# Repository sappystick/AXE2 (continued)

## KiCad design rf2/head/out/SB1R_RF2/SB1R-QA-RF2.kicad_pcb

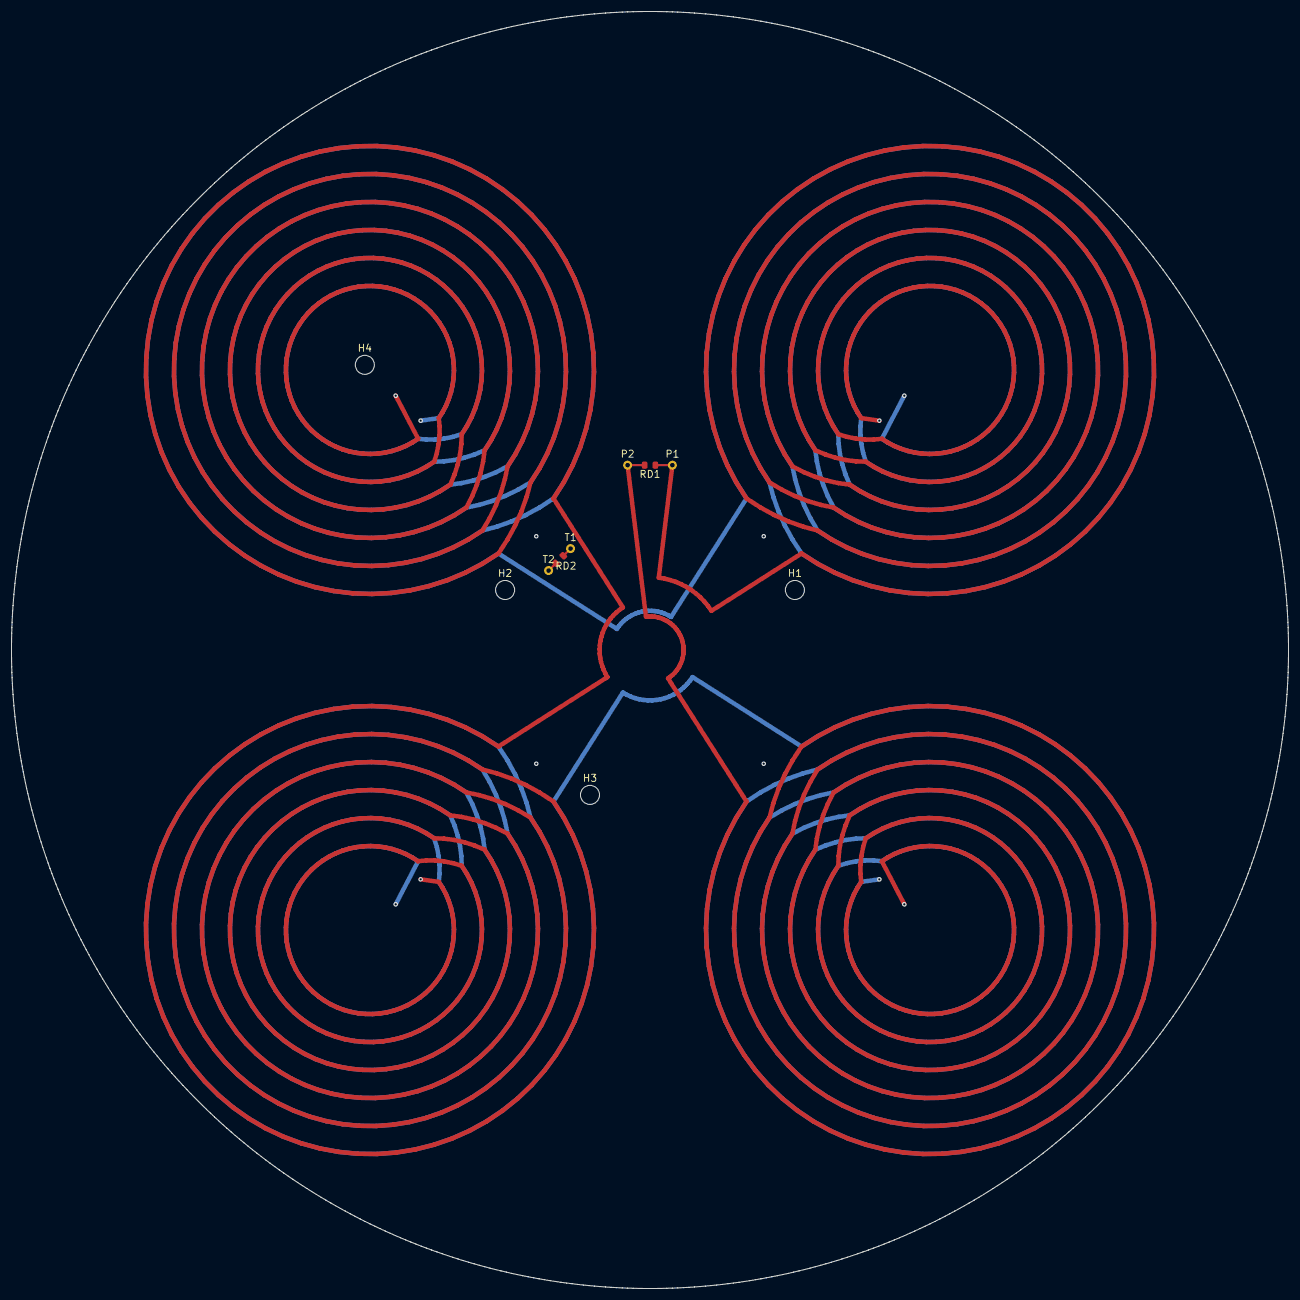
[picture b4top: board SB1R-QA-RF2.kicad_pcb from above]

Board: 4 copper layers, 228.0 x 228.0 mm, 10 parts (0 on the bottom side), 3 nets.

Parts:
H1, H2, H3, H4: MH_M3
P1, P2: LEAD_PAD
RD1, RD2: 680R 0.1% thin film 0805, non-magnetic terminatio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; R_0805_2012Metric
T1, T2: TRANSFER_PAD

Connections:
QA_COIL: P1.1, P2.1, RD1.1, RD1.2
QB_T1: RD2.1, T1.1
QB_T2: RD2.2, T2.1

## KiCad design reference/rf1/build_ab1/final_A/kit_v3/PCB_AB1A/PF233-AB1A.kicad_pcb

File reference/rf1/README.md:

# RF1: rigid-flex redesign, side experiment (started 2026-10-29)

**Status: MODELED side experiment, phase 1 done.** Not part of the sign-off, the pipeline, the regress suite or any release. The baseline design is read and never written: every input the study reads is recorded with its sha256 in `results/rf1_phase1.json` together with the baseline commit. Any generator that a later phase changes is first copied into `experiments/RF1_rigidflex/src/` and changed there.

**Fixed (owner, 2026-10-29):** receive coils SB1R-QA/QB, the HTA antenna, the six TX formers and their litz, every printed part. **Free:** how the electronics are split into boards and how they connect: flex, rigid-flex or the circular rigid boards.

## Concepts

| | A: catalog FFC (B12 decision) | B: soldered flex jumpers | C: head rigid-flex (RF1 main line) |
|---|---|---|---|
| What | separate rigid boards, 0.5 mm FFC + connectors at the duct edges | separate rigid boards, custom 2-layer flex strips soldered / hot-bar bonded to pads (no connector) | AB1A + AB1B + CB1D + LB1 one rigid-flex panel (6L rigid sections, 2L flex core), HTA a flex tail, SB1R leads a soldered flex jumper |
| Hand joints in the head (today 66) | 18 (LB1, HTA and SB1R wires stay; the link becomes 4 reflowed connectors) | 12 bonded ends | 5 |
| Boards testable alone | yes | yes | no (panel test + test pads) |
| Fab | standard | standard + simple flex | rigid-flex vendor, every change re-spins the panel |

## Phase 1 results (`rf1_study.py`, MODELED / mesh-checked)

| Question | Result |
|---|---|
| AB1 <-> CB1D link fit on the meshes (link_path_check, imported unchanged) | baseline IDC ribbon 6 / 16 FAIL; catalog FFC 0 / 14; rigid-flex hinge (0.2 mm, no connector) 0 / 14 |
| Headroom (rigid-flex hinge) | 10.4 mm under LB1 (ribbon -4.4, FFC 8.4), 7.2 mm under the septum (ribbon -2.6, FFC 5.2) |
| CB1D -> LB1 hinge, CB1D -> HTA tail | rise 10.6 / 15.9 mm, S-fold needs 8.0 mm at a 2.0 mm fold radius (10 x 0.2 mm): both fit; flex about 15 / 21 mm |
| Receive-coil lead pair, 60 mm | loop area 10.2 mm2 (AWG36 touching) to 60 mm2 (loose 1 mm) today, 3.0 mm2 fixed on a broadside flex pair; capacitance about 5 pF either way |
| Eddy rule 5 | the board graph is a tree (no closed loop around the axis); hatched planes in the hinges; FR4 / polyimide stiffeners only (the vendor also offers stainless and aluminium: excluded) |
| Vendor (Rigiflex pages, `ds/`) | D228 fits the 18 x 24 in panel; 0.10 / 0.10 mm trace / space covers our finest; 6L 1.6 mm rigid-flex with 1 oz is a listed build; polyimide er 4, DF 0.04, water absorption 2.9 % |

What this does **not** show yet: any change in leak, noise or detection. The loop-area ratio is geometry only; the pickup needs the TX field along the lead path (phase 2).

## Where the real improvement is

1. **Build quality and repeatability (large, near certain):** 66 -> 5 hand joints in the head; the receive-lead loop area becomes a fixed 3 mm2 instead of 10-60 mm2 that depends on dressing, so the air leak becomes a calibratable constant instead of a per-unit variable. This is the gain RF1 can deliver for sure.
2. **Receive chain clean-sheet (large, MODELED next):** the AB1 sections are laid out from scratch in RF1, so the known receive defects go in at the same time: VREF / VCM buffer stability (OPEN_ITEMS 30), OPA2211 input range (31), chip-orientation robustness (B11), header pad rings (33). These are performance items; the flex is what lets the layout start over without the header constraint.
3. **Digital noise next to the receive coils (medium, to be modeled):** the ADC SPI (SCLK >= 27.2 MHz) runs between hatched ground layers in the hinge instead of an open ribbon.
4. **Not changed by RF1:** TX (litz, 20 A, 460 V taps stay wire, rules 5 / 6), the shaft cords (a 356 mm telescoping stroke needs dynamic flex: not proposed), the neck and handle boards.

## Phases

1. **Done:** census, mesh fit, fold radii, lead loop area, loop check, vendor fit (`results/rf1_phase1.json`, `results/rf1_head_concept.png`).
2. Receive-lead pickup: copy `sbq_sim.py` into `src/`, add the flex-tail path and the TX field along it; leak and its spread (wire dress Monte Carlo vs fixed flex). Hinge crosstalk SCLK -> RX input.
3. Clean-sheet AB1 section: copy `afe_design.py` / `afe_layout.py` into `src/`, apply items 30 / 31 (isolation resistor or reference driver; VCM / amplifier choice) and the rotating decoupling group (B11); route with the repo router.
4. Rigid-flex board definition: one outline with rigid and flex regions, stackup drawing (6L rigid, 2L flex core, coverlay, FR4 stiffeners), hinge routing with hatched GND, fold-line keep-outs (no vias or pads within 1 mm of a fold); DRC with drc.py per region; KiCad 9 has no per-region stackup, so the fab drawing carries it.
5. Compare A / B / C on the same table (fit, leak, noise, joints, test, cost from real quotes) and decide; only then does anything move into the main design (B12).

## Phase 2 results (`rf1_phase2.py`, on a copy of the receive simulation; MODELED)

Receive-lead pickup, 300 units per case, peak mV at turn-off (the same scale as the board leak in `kit_v22/sbq_sim.json`; lead path ASSUMED):

| QA board | mean | sigma | 95 % of units below |
|---|---|---|---|
| AWG36 untwisted (dress varies) | -1.6 | 26.8 | 49.3 |
| AWG36 twisted (5-15 mm pitch) | -0.03 | 0.69 | 1.27 |
| flex broadside pair at the design orientation | 0.09 | 0.15 | 0.31 |
| flex at the worst orientation (routed carelessly) | 3.0 | - | - |
| board leak for comparison: aligned / 0.1 mm / 0.5 mm offset | 0.008 / 0.015 / 0.13 | | |

The lead pair is part of the receive null: untwisted wire alone is 100-1000 x the aligned board leak. Flex cuts the unit-to-unit spread 4-5 x against a good twisted pair, and its mean is a fixed offset (calibratable). The flex must be routed at the design orientation (loop plane along the field): rule for phase 4. QB: 15.6 / 0.63 / 0.08 mV sigma.

Clock crosstalk into the analog lines of the AB1 <-> CB1D link (2D finite-difference C and L, upper bounds on a 100 pF node, 3.3 V edge in 2 ns):

| victim | ribbon (today) | RF1 hinge (guard traces + ground layer) |
|---|---|---|
| MONO_IN, worst aggressor | 437 mV | 7.1 mV |
| MONO_IN from SCLK | 62 mV | 0.22 mV |
| VCM_OUT, worst aggressor | 215 mV | 1.4 mV |

## Cavity and potting (`rf1_cavity.py`, MODELED, envelope volumes)

With hinges instead of headers and three part swaps on CB1D (OKI-78SR module -> TI LMR36015 + Bourns SRN4018-6R8M; Pico 2 W on pins -> chip-down RP2354A without the radio; headers -> hinges), the tallest CB1D part is 2.5 mm (was 10.2) and the tallest AB1 part 1.6 mm (was the 4 mm header + 5 mm socket).

| layer | baseline | needs | saving |
|---|---|---|---|
| L1 gallery | 5.8 | 2.2 | 3.6 |
| L2 analog cell | 10.2 | 6.05 | 4.15 |
| L5 controller | 11.8 | 5.1 | 6.7 |

- **K-top (recommended):** L0-L4 keep their z (nothing near the receive coils moves); L5 shrinks 6.7 mm: head 47.1 -> 40.4 mm. L5 becomes a potted zone (syntactic silicone, 22.8 cm3, 13.7-18.3 g) instead of coat-only: the tube saves 13.7 g, so the head mass is about unchanged (0 to +4.6 g); the gain is protection (moisture, microphonics, better heat path than still air). To re-run: head_crosscheck, the HTA coupling (it moves 6.7 mm toward the formers), head thermal with the pour.
- **S (full shrink):** 14.5 mm (head 32.6 mm), but AB1, the septum and the carbonyl-iron absorber move 3.6-7.8 mm toward the receive coils: changes the receive null; not before sbq_sim / check_v22 / head_crosscheck say so.
- Potting: L1 gallery and L2 gel (fixed flex, no connector voids), L4 CI unchanged, L5 SYN (new), every hinge bend outside the pours, LB1 / HTA coat only.

## Phase 4: the head rigid-flex definition (`rf1_phase4.py`, MODELED)

- **Stackup:** 6-layer rigid sections (F, In1 hatched GND, In2, In3, In4 plane / +3V3D island, B) with the 2-layer flex core as In2 / In3: hinge signals leave on In2 over a hatched In3 ground. Rigid 1.602 mm, flex 0.186 mm (vendor: 1.6 / 0.2). LB1 goes 4 -> 6 layers; HTA stays a separate 4-layer board with a hot-bar flex tail (the roof stays removable).
- **Flattened panel:** CB1D at the centre, LB1 across its 15.2 mm S-fold, AB1A / AB1B at the ends of L-shaped 7 mm hinges that leave the CB1D duct edge either side of the LB1 hinge: 332 x 171 mm, fits the 457 x 610 mm panel; copper is 24.5 % of the box (expect a high panel price: get quotes).
- **Fold and transition rules F1-F8:** no via / pad within 1.0 mm of a transition; traces cross folds at 90 deg, no corners or width changes in a bend zone; cross-hatched flex ground; fold radius >= 2.0 mm, static only; FR4 / polyimide stiffeners only (rule 5); no 460 V net on any flex (rule 6); no rigid pour across a fold; ground guards on both sides of every analog hinge line. ASSUMED until the vendor and IPC-2223 confirm.
- **CB1D section:** Pico 2 W module and OKI-78SR leave; RP2354A (QFN-60) + 12 MHz crystal + core inductor + TLV755P 3.3 V and LMR36015 + SRN4018-6R8M come in, placed in the freed areas with 0.3 mm to every kept part (`results/rf1_cb1d_section.png`). The radio leaves with the Pico W (OPEN_ITEMS 42 settled by removal). CB1D is not re-routed in RF1 yet.

## Phase 3: clean-sheet AB1 (`src/ab1/`, MODELED)

`make_rf1_ab1.py` builds the RF1 generator as checked patches of the baseline `afe_design.py` / `afe_layout.py` / `afe_ripup.py`. Changes: hinge-exit lands (J2) and flex-jumper lands (J1) instead of headers; OPA2211 reference VBIAS = 2.5 V (REFOUT through OPA2365 half A, 10 ohm isolation, 1 uF); 1:2 divider into each ADC input (AIN+ 1.25 V DC = VCM); RF 820 ohm (total gain 41.5); 10 ohm isolation on the VCM buffer (OPEN_ITEMS 30); local TLV755P +3V3D next to the ADC island (the hinge no longer carries +3V3D; pin 3 is a ground).

Front-end check (`rf1_frontend_check.py`, against TI SBOS377L and the AD7389-4 Rev. 0): baseline **FAIL** (OPA2211 input 1.25 V, range 2.0-3.6 V); RF1 **PASS** (input 2.5 V, ADC common mode 1.25 V inside 0.2-2.3, offset 0 by construction, 38 % of the ADC differential range used vs 42 % baseline, divider noise 0.1 nV/rtHz vs 1.1 for the amplifier, closed-loop bandwidth 0.96 MHz vs the 318 kHz filter).

Routing (the repo's AB1 router, then the Freerouting step where it stalls; unchanged rules: track 0.15, clearance 0.16, via 0.508 / 0.254):

- **Routing status: AB1B routed: 0 open; KiCad 9 DRC 0 errors / 0 unconnected (20 dangling-track warnings, the baseline has 19); independent DRC 0 fails, minimum clearance 0.204 mm** (`build_ab1/final_B/`, `results/rf1_ab1_route.json`).
- **AB1A routed: 0 open; KiCad 9 DRC 0 errors / 0 unconnected (26 dangling-track warnings); independent DRC 0 fails, minimum clearance 0.165 mm; Gerber edge check OK** (`build_ab1/final_A/`). The repo router and repair loop left 1 net open (OUT_GY: U1.7 to RF2; 9 hash-seed routes all left the same net, so the placement, not the net order, was the limit). The Freerouting step (`src/pcb/freeroute.py`, Freerouting 2.4.1, pinned jar) ripped OUT_GY and re-routed it with the repo rules: 62 vias. It also closed VBIAS_O (UB to RISA), which the exported board had open although the router report did not list it.
- Exporter fix found on the way (RF1 copy, patched in `make_rf1_ab1.py`): the stub-to-pad test treated an SMD pad as a sharp rectangle, so a track ending on the rectangle corner of a rounded pad (CVB.2) stayed about 4 um off the copper; KiCad joined it, the independent DRC did not. The baseline `src/pcb/afe_export.py` has the same test (no baseline board triggers it today): OPEN_ITEMS 45.
- One command per board: `FR_RIP=OUT_GY experiments/RF1_rigidflex/src/ab1/finalize_rf1_ab1.sh A build_ab1/rep_A_fin_A_1 "<PUT>"` (export, Freerouting, KiCad Gerbers into `final_<B>/GERBER_AB1<B>`, KiCad DRC, independent DRC, Gerber edge check); then `src/ab1/record_route.py`, `rf1_phase4.py` (F1 now reads the final board), `rf1_summary.py`.
- How: the hinge exit (J2 lands) sits where the baseline header was (east edge, next to the ADC) and the hinge folds up there; the north exit toward the duct left 3-15 nets open. Placement of the RF1 parts (and, on AB1B, D2 / RF1 / CF1 nudged in a 2 mm window) is automatic: `src/ab1/autoplace_rf1.py` (pads and bodies checked, 0.5 mm corridor margin, caps anchored to their pins) and `src/ab1/repair_loop.py` (re-places only the parts within 2.5-5.5 mm of a stuck pin, keeps a result only if fewer nets are open).
- Tried and dropped (recorded in the generator as options, off): matched AIN- dividers (more parts, 8-15 open), swapped buffer halves (the LDO then blocks the +3V3D island), no local LDO on AB1A (5-8 open), the north hinge exit (3-15 open).

## Baseline defect found here (recorded in docs/CORRECTIONS.md, 2026-10-29)

The committed AD7389-4 AB1 biases the OPA2211 inputs at VCM = 1.25 V, below their 2.0 V minimum on a single 5 V supply (TI SBOS377L). RF1 fixes it (phase 3).

## Files

- `rf1_study.py` phase 1 study; `rf1_figure.py` the figure; `rf1_phase2.py` lead pickup and crosstalk; `rf1_cavity.py` condensation and potting;
  `src/ab1/make_rf1_ab1.py` the clean-sheet AB1 as checked patches of the baseline generator (writes the RF1 copies `afe_design.py`, `afe_layout.py`, `afe_ripup.py`);
  `rf1_phase4.py` stackup, flattened panel, fold rules, CB1D section; `results/` outputs; `ds/` the Rigiflex pages (owner-supplied, 2026-10-29); `src/sbq_sim_baseline_copy.py` the receive simulation copy.

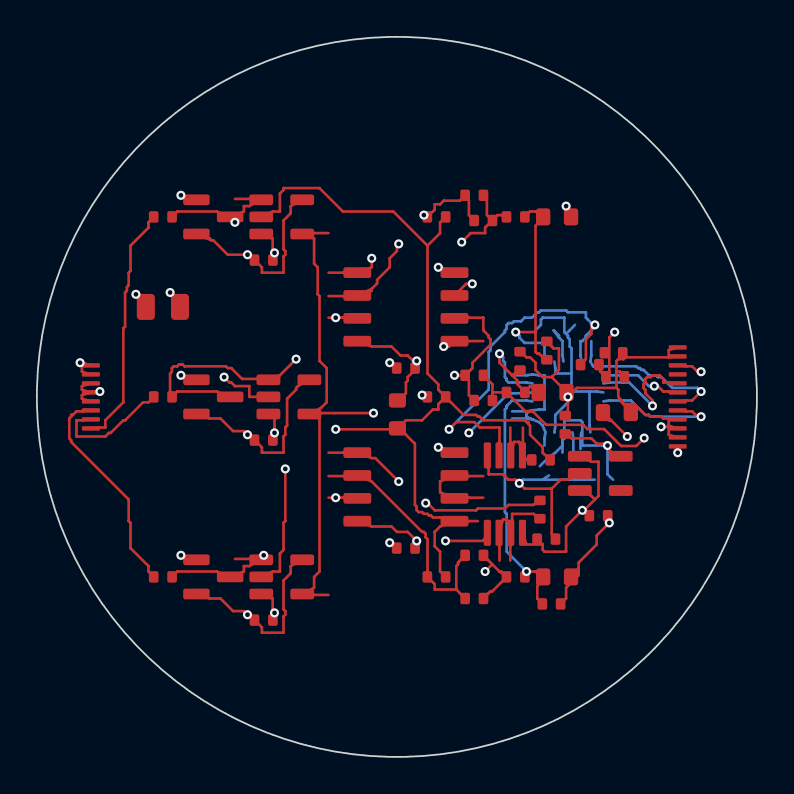
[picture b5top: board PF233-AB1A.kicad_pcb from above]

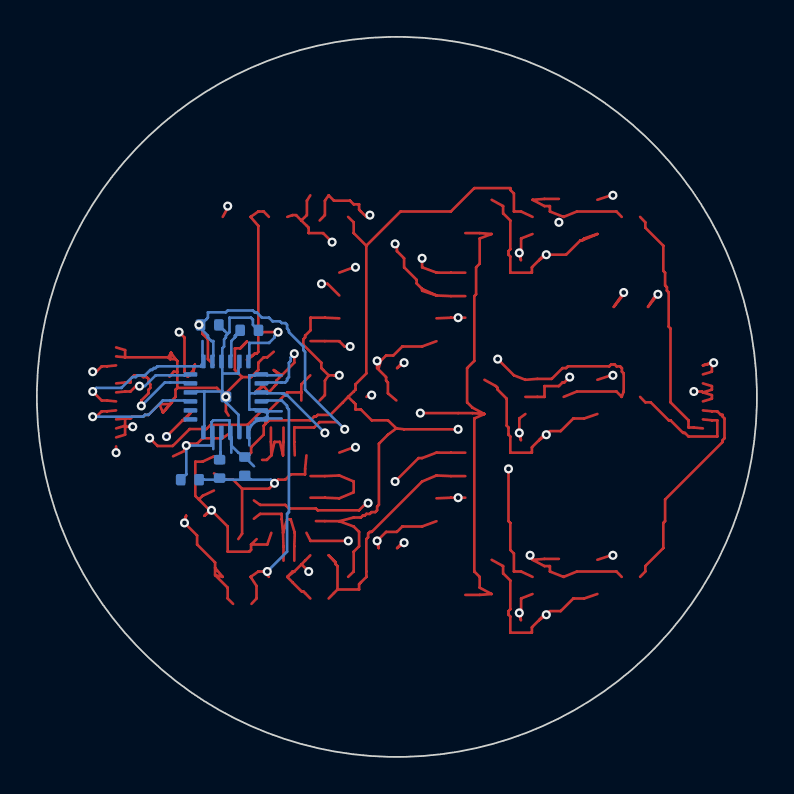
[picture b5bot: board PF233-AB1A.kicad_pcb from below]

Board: 6 copper layers, 40.0 x 40.0 mm, 55 parts (6 on the bottom side), 32 nets.

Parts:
CAAF1, CAAF2, CAAF3: 1n; C_0603_1608Metric
CB1: 10u; C_0805_2012Metric
CBD: 100n; C_0402_1005Metric
CDF: 100n; C_0402_1005Metric
CF1, CF2, CF3: 22p; C_0402_1005Metric
CLI: 1u; C_0402_1005Metric
CLO: 1u; C_0402_1005Metric
CO1, CO2: 100n; C_0402_1005Metric
CRC: 100n; C_0402_1005Metric
CRF: 1u; C_0402_1005Metric
CRG: 1u; C_0402_1005Metric
CSW1, CSW2, CSW3: 100n; C_0402_1005Metric
CVB: 1u; C_0603_1608Metric
CVC: 1u; C_0402_1005Metric
CVL: 1u; C_0402_1005Metric
CVM: 1u; C_0603_1608Metric
D1, D2, D3: BAV199; SOT-23
J1: RF1 receive-coil flex jumper lands 8p; FPC_8_P0.5
J2: RF1 rigid-flex hinge exit 12p; FPC_12_P0.5
RAAF1, RAAF2, RAAF3: 1k; R_0402_1005Metric
RB1, RB2, RB3: 1k; R_0402_1005Metric
RD1, RD2: 100k; R_0402_1005Metric
RF1, RF2, RF3: 820; R_0402_1005Metric
RG1, RG2, RG3: 10; R_0402_1005Metric
RISA: 10; R_0402_1005Metric
RISB: 10; R_0402_1005Metric
RS1, RS2: 100; R_0402_1005Metric
RS3: 1000; R_0402_1005Metric
SW1, SW2, SW3: 74LVC1G66; SOT-23-5
U1, U2: OPA2211; SOIC-8_3.9x4.9mm_P1.27mm
UA1: AD7389-4; CP-24-25_ADI_LFCSP-24-1EP_4x4mm_P0.5mm_EP0.61x0.61mm
UB: OPA2365; MSOP-8_3x3mm_P0.65mm
ULD: TLV755P33; SOT-23-5

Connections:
+3V3D: CLO.1, CVC.1, CVL.1, UA1.2, UA1.4, ULD.5
+5VA: CB1.1, CBD.1, CLI.1, CO1.1, CO2.1, CSW1.1, CSW2.1, CSW3.1, D1.2, D2.2, D3.2, J2.1, SW1.5, SW2.5, SW3.5, U1.8, U2.8, UB.8, ULD.1, ULD.3
ADCIN_GX: CAAF1.1, RAAF1.2, RB1.1, UA1.13
ADCIN_GY: CAAF2.1, RAAF2.2, RB2.1, UA1.11
ADCIN_X8: CAAF3.1, RAAF3.2, RB3.1, UA1.9
BLANK: J2.10, SW1.4, SW2.4, SW3.4
CS: J2.6, UA1.18
FB_GX: CF1.1, RF1.1, RG1.1, U1.2
FB_GY: CF2.1, RF2.1, RG2.1, U1.6
FB_X8: CF3.1, RF3.1, RG3.1, U2.2
GND: CAAF1.2, CAAF2.2, CAAF3.2, CB1.2, CBD.2, CDF.2, CLI.2, CLO.2, CO1.2, CO2.2, CRC.2, CRF.2, CRG.2, CSW1.2, CSW2.2, CSW3.2, CVB.2, CVC.2, CVL.2, CVM.2, D1.1, D2.1, D3.1, J1.7, J1.8, J2.2, J2.3, J2.4, J2.11, J2.12, RB1.2, RB2.2, RB3.2, RD2.2, SW1.3, SW2.3, SW3.3, U1.4, U2.4, UA1.1, UA1.5, UA1.14, UA1.16, UA1.21, UA1.25, UB.4, ULD.2
IN_GX: D1.3, RS1.2, SW1.1, U1.3
IN_GY: D2.3, RS2.2, SW2.1, U1.5
IN_X8: D3.3, RS3.2, SW3.1, U2.3
OUT_GX: CF1.2, RAAF1.1, RF1.2, U1.1
OUT_GY: CF2.2, RAAF2.1, RF2.2, U1.7
OUT_X8: CF3.2, RAAF3.1, RF3.2, U2.1
RAW_GX: J1.1, RS1.1
RAW_GY: J1.2, RS2.1
RAW_X8: J1.3, RS3.1
REFCAP: CRC.1, UA1.15
REGCAP: CRG.1, UA1.3
SCLK: J2.5, UA1.22
SDO1: J2.7, UA1.19
SDO2: J2.8, UA1.20
SPARE_OUT_U2: U2.6, U2.7
VBIAS: CVB.1, J1.4, J1.5, J1.6, RG1.2, RG2.2, RG3.2, RISA.2, SW1.2, SW2.2, SW3.2, U2.5
VBIAS_O: RISA.1, UB.1, UB.2
VCM: CVM.1, RISB.2, UA1.6, UA1.7, UA1.8, UA1.10, UA1.12
VCM_DIV: CDF.1, RD1.2, RD2.1, UB.5
VCM_O: RISB.1, UB.6, UB.7
VREF_RAW: CRF.1, RD1.1, UA1.17, UB.3
